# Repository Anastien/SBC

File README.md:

# SBC
My design of a single board computer.

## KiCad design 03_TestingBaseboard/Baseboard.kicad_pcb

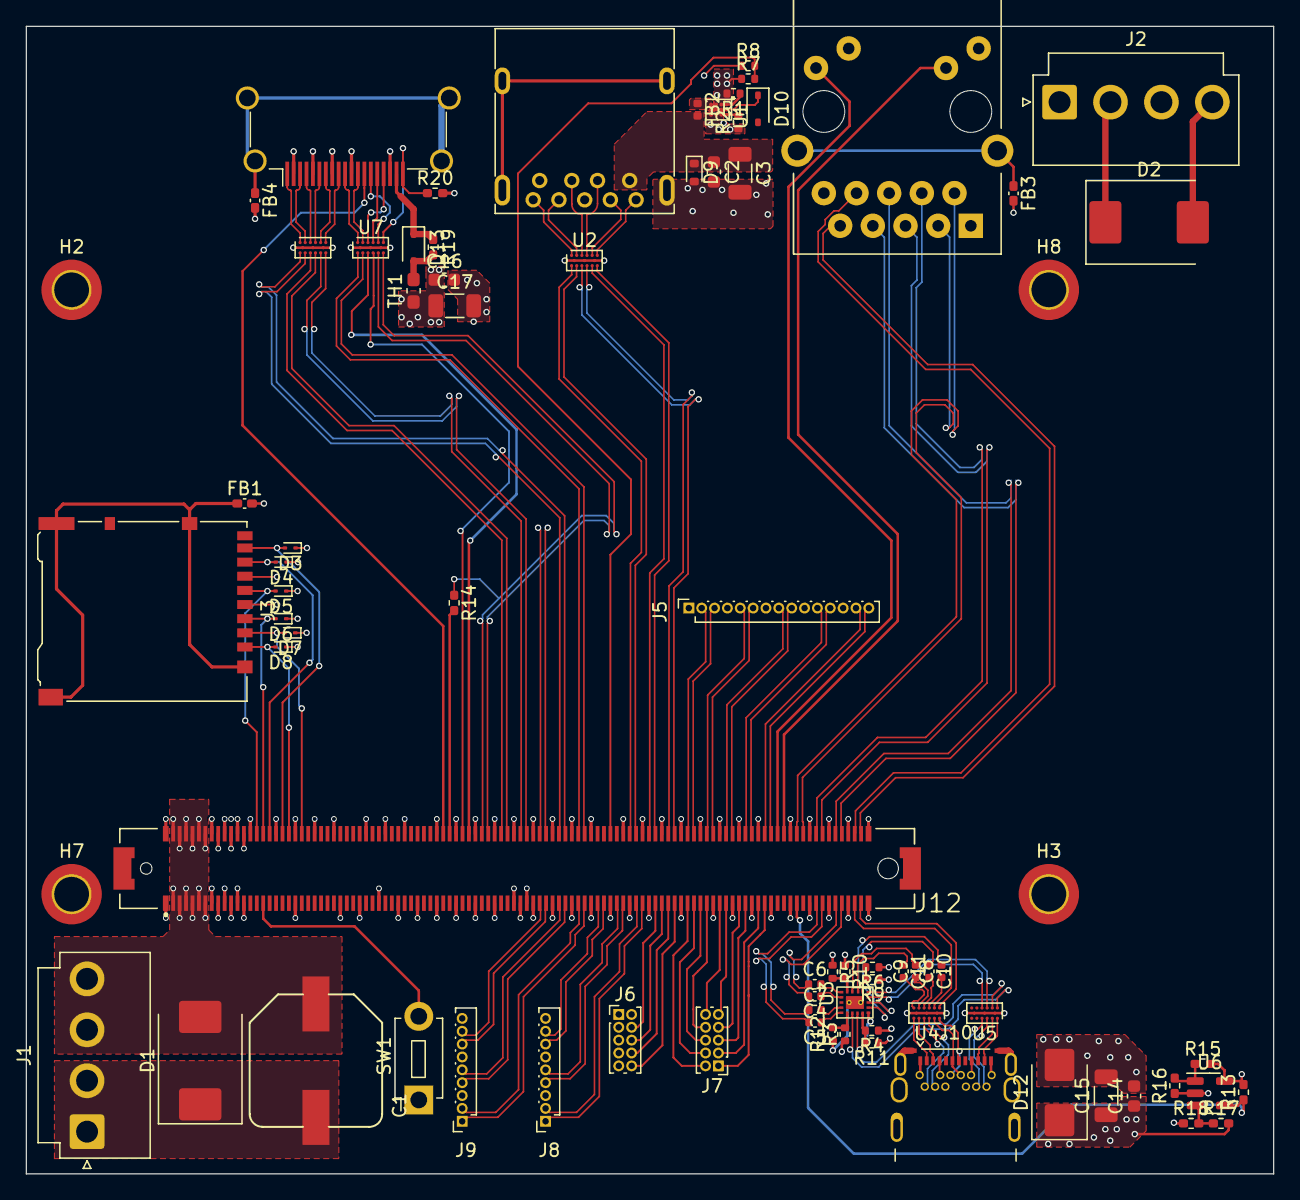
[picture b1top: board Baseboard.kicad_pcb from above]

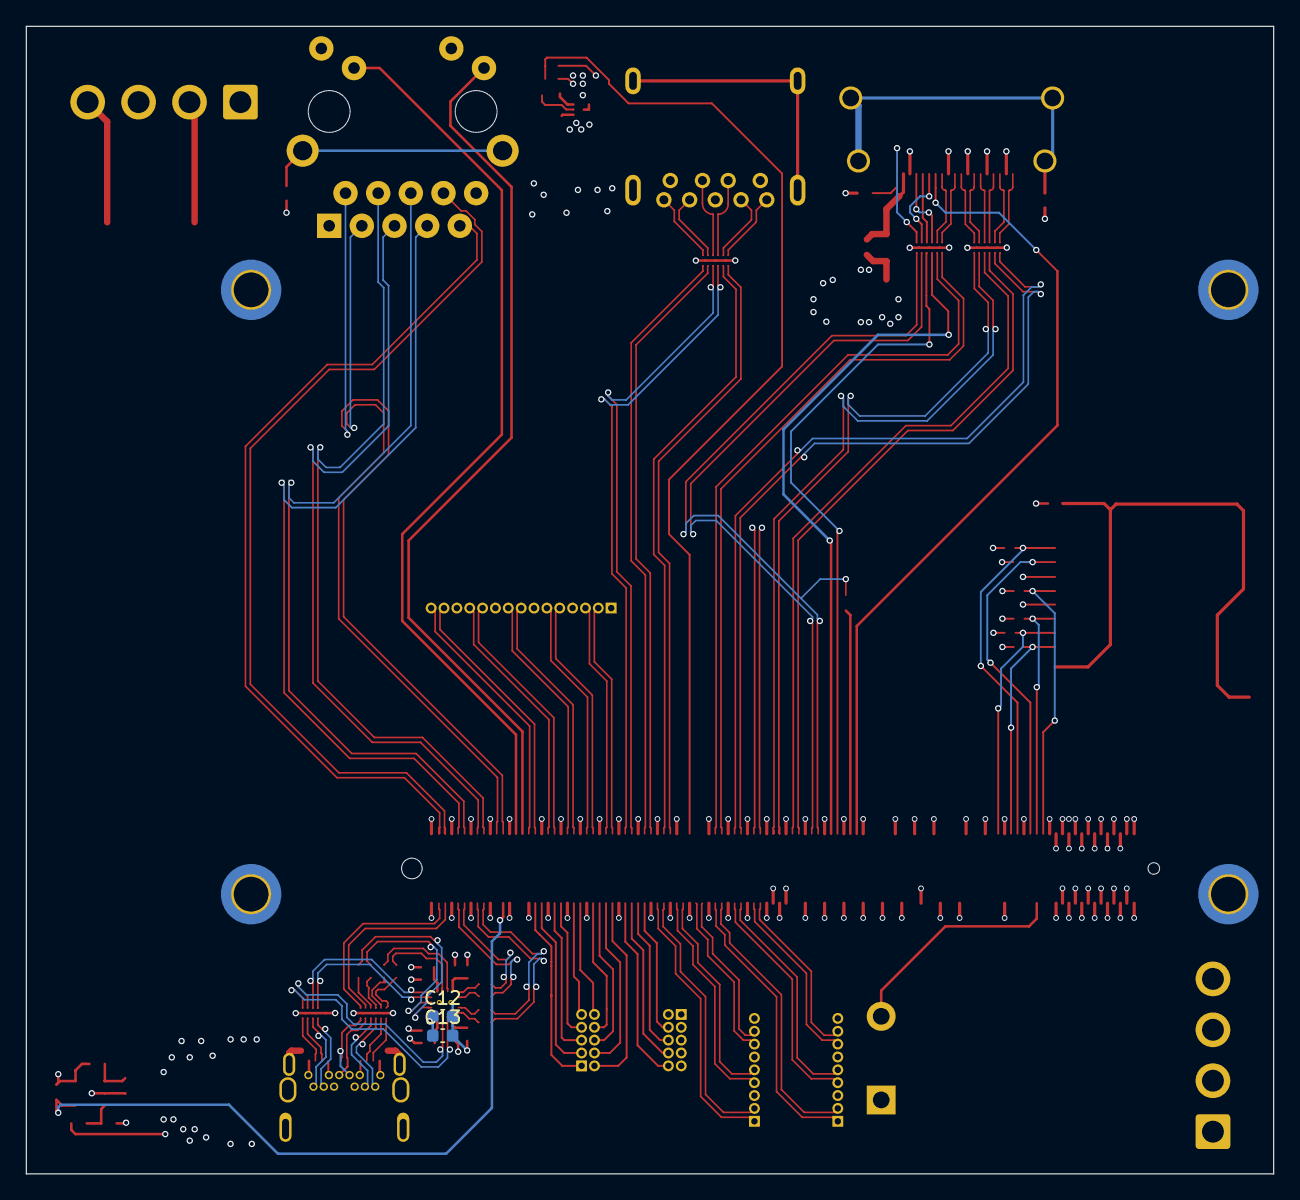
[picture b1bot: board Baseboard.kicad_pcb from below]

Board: 4 copper layers, 97.0 x 89.2 mm, 80 parts (2 on the bottom side), 146 nets.

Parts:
C1: 220uF; EEE-FK1H221GP
C2, C12, C13, C14, C16: 220nF; C_0603_1608Metric
C3, C15, C17: 10uF; C_1206_3216Metric
C4, C5, C6, C7, C8, C9, C10, C11: 220nF; C_0402_1005Metric
D1, D2: D_TVS; D_SMC
D3, D4, D5, D6, D7, D8: ESD9B3.3ST5G; D_SOD-923
D9: ESD5Zxx; D_SOD-523
D10, D13: SD0603S040S0R2; D_SOD-323
D12: SM6T24A; D_SMB
FB1, FB3, FB4: FerriteBead; L_0402_1005Metric_Pad0.77x0.64mm_HandSolder
FB2: FerriteBead_Small; L_0402_1005Metric
H2, H3, H7, H8: MountingHole_Pad; MountingHole_2.7mm_M2.5_DIN965_Pad_TopBottom
J1, J2: B4P-VH(LF)(SN); JST_VH_B4P-VH-B_1x04_P3.96mm_Vertical
J3: Micro_SD_Card_Det; microSD_HC_Hirose_DM3AT-SF-PEJM5
J4: USB3_A; USB3_A_Molex_48393-001
J5: Conn_01x15_Pin; PinSocket_1x15_P1.00mm_Vertical
J6, J7: Conn_02x05_Odd_Even; PinHeader_2x05_P1.00mm_Vertical
J8, J9: Conn_01x09_Pin; PinSocket_1x09_P1.00mm_Vertical
J10: USB_C_Receptacle; USB_C_Receptacle_CNCTech_C-ARA1-AK51X
J11: RJ45_RB1-125B8G1A; RJ45_UDE_RB1-125B8G1A
J12: 3-1827253-6; CONN_3-1827253-6
J13: HDMI_A; HDMI_A_Amphenol_10029449-x01xLF_Horizontal
R1: 10K; R_0402_1005Metric
R2, R7, R8: 24.3K; R_0402_1005Metric
R3, R4, R5, R6, R9, R10, R11, R12: 49.9; R_0402_1005Metric
R13, R14, R15, R16, R17, R18, R19: 49.9; R_0402_1005Metric_Pad0.72x0.64mm_HandSolder
R20: 1M; R_0402_1005Metric_Pad0.72x0.64mm_HandSolder
SW1: SW_Push; SW_PUSH_1P1T_6x3.5mm_H4.3_APEM_MJTP1243
TH1: Thermistor_PTC_US; Fuse_0603_1608Metric_Pad1.05x0.95mm_HandSolder
U1: NX5P3090; WLCSP12_1.65X1.35
U2, U4, U5, U7, U8: PCMF3USB3S; Nexperia_WLCSP-15_6-3-6_2.37x1.17mm_Layout6x3_P0.4mm
U3: PTN36043ABX; DHX2QFN18
U6: LM397; SOT-23-5

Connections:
+1V8: C12.1, C13.1, R3.1, R4.1, R5.1, R6.1, U3.5 (VDD1V8)
+5V: C16.1, C17.1, D2.2 (A2), J2.3, J2.4, R1.2, R7.1, R13.2, R15.2, TH1.1, U1.B1 (VIN1), U1.B2 (VIN2), U1.C1 (VIN3), U6.5 (V+)
/BASEBOARD/AP_N: C6.2, U3.14 (TX_AP-)
/BASEBOARD/AP_P: C4.1, U3.15 (TX_AP+)
/BASEBOARD/C_VBUS: C14.1, C15.1, D12.1 (A1), J10.A4 (VBUS), J10.A9 (VBUS), J10.B4 (VBUS), J10.B9 (VBUS), R17.2
/BASEBOARD/D1_N: J4.2 (D-), U2.A4 (CH2_IN-)
/BASEBOARD/D1_P: J4.3 (D+), U2.A3 (CH2_IN+)
/BASEBOARD/HC_N: J13.12 (CK-), U7.A2 (CH1_IN-)
/BASEBOARD/HC_P: J13.10 (CK+), U7.A1 (CH1_IN+)
/BASEBOARD/HDMI_5V: D13.1 (K), J13.18 (+5V), R19.1
/BASEBOARD/HEAC_N: J13.19 (HPD), R20.1, U7.A6 (CH3_IN-)
/BASEBOARD/HEAC_P: J13.14 (UTILITY), U7.A5 (CH3_IN+)
/BASEBOARD/HSCL: J13.15 (SCL), U7.A4 (CH2_IN-)
/BASEBOARD/HSDA: J13.16 (SDA), U7.A3 (CH2_IN+)
/BASEBOARD/HTX0_N: J13.9 (D0-), U8.A6 (CH3_IN-)
/BASEBOARD/HTX0_P: J13.7 (D0+), U8.A5 (CH3_IN+)
/BASEBOARD/HTX1_N: J13.6 (D1-), U8.A4 (CH2_IN-)
/BASEBOARD/HTX1_P: J13.4 (D1+), U8.A3 (CH2_IN+)
/BASEBOARD/HTX2_N: J13.3 (D2-), U8.A2 (CH1_IN-)
/BASEBOARD/HTX2_P: J13.1 (D2+), U8.A1 (CH1_IN+)
/BASEBOARD/LED0: J11.L3, J12.B97 (SPI_CS#_(**))
/BASEBOARD/LED1: J11.L1, J12.B96 (RSVD)
/BASEBOARD/RX1_N: J4.5 (SSRX-), U2.A1 (CH1_IN+)
/BASEBOARD/RX1_P: J4.6 (SSRX+), U2.A2 (CH1_IN-)
/BASEBOARD/RXC_N: U3.3 (RX_CON_1-), U5.C2 (CH1_OUT-)
/BASEBOARD/RXC_P: U3.2 (RX_CON_1+), U5.C1 (CH1_OUT+)
/BASEBOARD/RX_C2_N: U3.8 (RX_CON_2-), U5.C4 (CH2_OUT-)
/BASEBOARD/RX_C2_P: U3.9 (RX_CON_2+), U5.C3 (CH2_OUT+)
/BASEBOARD/R_AP_N: C7.2, U3.17 (RX_AP-)
/BASEBOARD/R_AP_P: C5.1, U3.18 (RX_AP+)
/BASEBOARD/TX1_N: J4.8 (SSTX-), U2.A5 (CH3_IN+)
/BASEBOARD/TX1_P: J4.9 (SSTX+), U2.A6 (CH3_IN-)
/BASEBOARD/TXC1_N: C10.1, U3.7 (TX_CON_1-)
/BASEBOARD/TXC1_P: C8.2, U3.6 (TX_CON_1+)
/BASEBOARD/TXC2_N: C11.1, U3.11 (TX_CON_2-)
/BASEBOARD/TXC2_P: C9.2, U3.12 (TX_CON_2+)
/BASEBOARD/U1RX1_N: J10.B11 (RX1+), U4.A4 (CH2_IN-)
/BASEBOARD/U1RX1_P: J10.B10 (RX1-), U4.A3 (CH2_IN+)
/BASEBOARD/U1_VBUS: C2.1, C3.1, D9.1 (K), FB2.2, J4.1 (VBUS)
/BASEBOARD/U2D_N: J10.A6 (D+), J10.B6 (D+), U4.A2 (CH1_IN-)
/BASEBOARD/U2D_P: J10.A7 (D-), J10.B7 (D-), U4.A1 (CH1_IN+)
/BASEBOARD/U2RX2_N: J10.A10 (RX2-), U5.A2 (CH1_IN-)
/BASEBOARD/U2RX2_P: J10.A11 (RX2+), U5.A1 (CH1_IN+)
/BASEBOARD/U2TX1_N: J10.A3 (TX1-), U4.A5 (CH3_IN+)
/BASEBOARD/U2TX1_P: J10.A2 (TX1+), U4.A6 (CH3_IN-)
/BASEBOARD/U2TX2_N: J10.B3 (TX2-), U5.A4 (CH2_IN-)
/BASEBOARD/U2TX2_P: J10.B2 (TX2+), U5.A3 (CH2_IN+)
/BASEBOARD/_TXC1_N: C10.2, U4.C4 (CH2_OUT-)
/BASEBOARD/_TXC1_P: C8.1, U4.C3 (CH2_OUT+)
/BASEBOARD/_TXC2_N: C11.2, U4.C6 (CH3_OUT-)
DSI_CLK_N: J5.3, J12.B83 (eDP/LVDS_BKLT_CTRL)
DSI_CLK_P: J5.2, J12.B82 (DDI0_PAIR3-)
DSI_D0_N: J5.12, J12.B92 (DDI0_PAIR5-_(*))
DSI_D0_P: J5.11, J12.B91 (DDI0_PAIR5+_(*))
DSI_D1_N: J5.9, J12.B89 (DD0_HPD)
DSI_D1_P: J5.8, J12.B88 (BIOS_DIS1#)
DSI_D2_N: J5.15, J12.B95 (DDI0_DDC_AUX_SEL)
DSI_D2_P: J5.14, J12.B94 (DDI0_PAIR6-_(*))
DSI_D3_N: J5.6, J12.B86 (VCC_5V_SBY)
DSI_D3_P: J5.5, J12.B85 (VCC_5V_SBY)
GBE0_MDI0_N: J11.R3 (TD1-), J12.B100 (GND(FIXED))
GBE0_MDI0_P: J11.R2 (TD1+), J12.B99 (DDI0_CTRLDATA_AUX-)
GBE0_MDI1_N: J11.R5 (TD2-), J12.B103 (SLEEP#)
GBE0_MDI1_P: J11.R4 (TD2+), J12.B102 (FAN_TACHIN)
GBE0_MDI2_N: J11.R7 (TD3-), J12.B106 (VCC_12V)
GBE0_MDI2_P: J11.R6 (TD3+), J12.B105 (VCC_12V)
GBE0_MDI3_N: J11.R9 (TD4-), J12.B109 (VCC_12V)
GBE0_MDI3_P: J11.R8 (TD4+), J12.B108 (VCC_12V)
GND: C1.2, C2.2, C3.2, C12.2, C13.2, C14.2, C15.2, C16.2, C17.2, D1.1 (A1), D2.1 (A1), D3.1 (A1), D4.1 (A1), D5.1 (A1), D6.1 (A1), D7.1 (A1), D8.1 (A1), D9.2 (A), D12.2 (A2), FB1.2, FB3.2, FB4.2, J1.1, J1.2, J2.1, J2.2, J3.6 (VSS), J4.4 (GND), J4.7 (DRAIN), J4.10 (SHIELD), J5.1, J5.4, J5.7, J5.10, J5.13, J6.1, J6.3, J6.5, J6.7, J6.9, J8.3, J8.6, J8.9, J9.3, J9.6, J9.9, J10.A1 (GND), J10.A12 (GND), J10.B1 (GND), J10.B12 (GND), J10.S1 (SHIELD), J12.A1 (GND(FIXED)), J12.A8 (GBE0_LINK#), J12.A9 (GBE0_MDI1-), J12.A10 (GBE0_MDI1+), J12.A11 (GND(FIXED)), J12.A12 (GBE0_MDI0-), J12.A13 (GBE0_MDI0+), J12.A21 (GND(FIXED)), J12.A28 ((S)ATA_ACT#), J12.A31 (GND(FIXED)), J12.A34 (BIOS_DIS0#), J12.A37 (USB6+), J12.A40 (USB1_RX_P), J12.A43 (USB1_TX_P), J12.A46 (USB1_DP), J12.A49 (EXCD0_CPPE#), J12.A52 (RSVD), J12.A55 (RSVD), J12.A56 (RSVD), J12.A57 (GND), J12.A58 (PCIE_TX3+), J12.A61 (PCIE_TX2+), J12.A64 (PCIE_TX1+), J12.A67 (GPI2), J12.A70 (GND(FIXED)), J12.A73 (eDP_TX1+/LVDS_A1+), J12.A76 (eDP_TX0-/LVDS_A2-), J12.A81 (eDP_TX3+/LVDS_A_CK+), J12.A86 (RSVD), J12.A89 (PCIE_CLK_REF-), J12.A92 (SPI_MISO_(**)), J12.A95 (SPI_MOSI_(**)), J12.A98 (SER0_TX_(**)), J12.A101 (SER1_TX_(**)), J12.A104 (VCC_12V), J12.A107 (VCC_12V), J12.A110 (GND(FIXED)), J12.B1 (GND(FIXED)), J12.B8 (LPC_DRQ0#_(*)), J12.B9 (LPC_DRQ1#_(*)), J12.B10 (LPC_CLK), J12.B11 (GND(FIXED)), J12.B12 (PWRBTN#), J12.B13 (SMB_CK), J12.B14 (SMB_DAT), J12.B18 (SUS_STAT#), J12.B21 (GND(FIXED)), J12.B24 (PWR_OK), J12.B27 (WDT), J12.B32 (SPKR), J12.B35 (THRM#), J12.B38 (USB_4_5_OC#), J12.B43 (USB3+), J12.B46 (USB1+), J12.B49 (SYS_RESET#), J12.B52 (RSVD), J12.B55 (RSVD), J12.B58 (PCIE_RX3+), J12.B61 (PCIE_RX2+), J12.B64 (PCIE_RX1+), J12.B67 (WAKE1#_(**)), J12.B72 (DDI0_PAIR0-), J12.B75 (DDI0_PAIR2+), J12.B78 (DDI0_PAIR4-_(*)), J12.B81 (DDI0_PAIR3+), J12.B84 (VCC_5V_SBY), J12.B87 (VCC_5V_SBY), J12.B90 (GND(FIXED)), J12.B93 (DDI0_PAIR6+_(*)), J12.B98 (DDI0_CTRLCLK_AUX+), J12.B101 (FAN_PWMOUT), J12.B104 (VCC_12V), J12.B107 (VCC_12V), J12.B110 (GND(FIXED)), J13.2 (D2S), J13.5 (D1S), J13.8 (D0S), J13.11 (CKS), J13.17 (GND), R2.1, R8.1, R9.1, R10.1, R11.1, R12.1, R16.1, R18.1, R20.2, SW1.1, U1.B3 (GND1), U1.C3 (GND2), U1.D3 (GND3), U2.B1 (GND_CH1), U2.B2 (GND_CH2), U2.B3 (GND_CH3), U3.19 (GND), U4.B1 (GND_CH1), U4.B2 (GND_CH2), U4.B3 (GND_CH3), U5.B1 (GND_CH1), U5.B2 (GND_CH2), U5.B3 (GND_CH3), U6.2 (V-), U7.B1 (GND_CH1), U7.B2 (GND_CH2), U7.B3 (GND_CH3), U8.B1 (GND_CH1), U8.B2 (GND_CH2), U8.B3 (GND_CH3)
HDMI_AUX_N: J12.B50 (CB_RESET#), R14.1, U7.C6 (CH3_OUT-)
HDMI_AUX_P: J12.B51 (GND(FIXED)), U7.C5 (CH3_OUT+)
HDMI_CEC: J12.B44 (USB_0_1_OC#), J13.13 (CEC)
HDMI_HDP: J12.B45 (USB1-), R14.2
HDMI_SCL: J12.B47 (EXCD1_PERST#), U7.C4 (CH2_OUT-)
HDMI_SDA: J12.B48 (EXCD1_CPPE#), U7.C3 (CH2_OUT+)
HDMI_TX0_N: J12.B56 (RSVD), U8.C6 (CH3_OUT-)
HDMI_TX0_P: J12.B57 (GPO2), U8.C5 (CH3_OUT+)
HDMI_TX1_N: J12.B54 (GPO1), U8.C4 (CH2_OUT-)
HDMI_TX1_P: J12.B53 (RSVD), U8.C3 (CH2_OUT+)
HDMI_TX2_N: J12.B62 (PCIE_RX2-), U8.C2 (CH1_OUT-)
HDMI_TX2_P: J12.B63 (GPO3), U8.C1 (CH1_OUT+)
HDMI_TX3_N: J12.B66 (WAKE0#), U7.C2 (CH1_OUT-)
HDMI_TX3_P: J12.B65 (PCIE_RX1-), U7.C1 (CH1_OUT+)
HOST_PCIE1_CLK_N: J9.1, J12.A66 (GND)
HOST_PCIE1_CLK_P: J9.2, J12.A65 (PCIE_TX1-)
HOST_PCIE2_CLK_N: J8.7, J12.A69 (PCIE_TX0-)
HOST_PCIE2_CLK_P: J8.8, J12.A68 (PCIE_TX0+)
unnamed: D10.1 (K), U1.A2 (#FLT)
unnamed: D13.2 (A), R19.2, TH1.2
unnamed: FB3.1, J11.SH
unnamed: FB4.1, J13.SH
unnamed: FB1.1, J3.11 (SHIELD)
unnamed: R1.1, U1.A1 (EN)
unnamed: R2.2, U1.A3 (IL)
unnamed: FB2.1, U1.C2 (VBUS1), U1.D1 (VBUS2), U1.D2 (VBUS3)
unnamed: R3.2, R12.2, U3.1 (RXDE)
unnamed: R6.2, R9.2, U3.10 (RXEQ)
unnamed: R5.2, R10.2, U3.13 (TXDE)
unnamed: R4.2, R11.2, U3.4 (TXEQ)
unnamed: C9.1, U4.C5 (CH3_OUT+)
unnamed: R17.1, R18.2, U6.3 (+)
unnamed: R15.1, R16.2, U6.1 (-)
PCIE1_RXN: J9.8, J12.A59 (PCIE_TX3-)
PCIE1_RXP: J9.7, J12.A60 (GND(FIXED))
PCIE1_TXN: J9.5, J12.A62 (PCIE_TX2-)
PCIE1_TXP: J9.4, J12.A63 (GPI1)
PCIE2_RXN: J8.4, J12.A72 (eDP_TX2-/LVDS_A0-)
PCIE2_RXP: J8.5, J12.A71 (eDP_TX2+/LVDS_A0+)
PCIE2_TXN: J8.1, J12.A75 (eDP_TX0+/LVDS_A2+)
PCIE2_TXP: J8.2, J12.A74 (eDP_TX1-/LVDS_A1-)
SD2_CLK: D5.2 (A2), J3.5 (CLK), J12.B15 (SMB_ALERT#)
SD2_CMD: D6.2 (A2), J3.3 (CMD), J12.B16 (SATA1_TX+)
SD2_D0: D4.2 (A2), J3.7 (DAT0), J12.B17 (SATA1_TX-)
SD2_D1: D3.2 (A2), J3.8 (DAT1), J12.B19 (SATA1_RX+)
SD2_D2: D8.2 (A2), J3.1 (DAT2), J12.B20 (SATA1_RX-)
SD2_D3: D7.2 (A2), J3.2 (DAT3/CD), J12.B22 (USB_SSTX0-)
SPI1_MISO: J6.4, J12.A77 (eDP/LVDS_VDD_EN)
SPI1_MOSI: J6.6, J12.A78 (LVDS_A3+)
SPI1_SCLK: J6.10, J12.A80 (GND(FIXED))
SPI1_SSO: J6.8, J12.A79 (LVDS_A3-)
SPI2_MISO: J7.2, J12.A82 (eDP_TX3-/LVDS_A_CK-)
SPI2_MOSI: J7.4, J12.A83 (eDP_AUX+/LVDS_I2C_CK)
SPI2_SCLK: J7.8, J12.A85 (GPI3)
SPI2_SSO: J7.6, J12.A84 (eDP_AUX-/LVDS_I2C_DAT)
SYS_NRST: J12.A16 (SATA0_TX+), SW1.2
UART1_RXD: J7.3, J12.A93 (GPO0)
UART1_TXD: J7.1, J12.A94 (SPI_CLK_(**))
UART2_RXD: J7.9, J12.A88 (PCIE_CLK_REF+)
UART2_TXD: J7.10, J12.A87 (eDP_HPD)
UART3_RXD: J7.7, J12.A90 (GND(FIXED))
UART3_TXD: J7.5, J12.A91 (SPI_POWER)
USB1_DN: J12.B79 (eDP/LVDS_BKLT_EN), U2.C4 (CH2_OUT-)
USB1_DP: J12.B80 (GND(FIXED)), U2.C3 (CH2_OUT+)
USB1_RX_N: J12.B73 (DDI0_PAIR1+), U2.C1 (CH1_OUT+)
USB1_RX_P: J12.B74 (DDI0_PAIR1-), U2.C2 (CH1_OUT-)
USB1_TX_N: J12.B76 (DDI0_PAIR2-), U2.C5 (CH3_OUT+)
USB1_TX_P: J12.B77 (DDI0_PAIR4+_(*)), U2.C6 (CH3_OUT-)
USB1_VBUS: J12.B70 (GND(FIXED)), R7.2, R8.2
USB2_DN: J12.A108 (VCC_12V), U4.C2 (CH1_OUT-)
USB2_DP: J12.A109 (VCC_12V), U4.C1 (CH1_OUT+)
USB2_RX_N: C7.1, J12.A102 (SER1_RX_(**))
USB2_RX_P: C5.2, J12.A103 (LID#)
USB2_TX_N: C6.1, J12.A105 (VCC_12V)
USB2_TX_P: C4.2, J12.A106 (VCC_12V)
USB2_VBUS: J12.A99 (SER0_RX_(**)), R13.1, U6.4
VIN: C1.1, D1.2 (A2), J1.3, J1.4, J12.A2 (GBE0_MDI3-), J12.A3 (GBE0_MDI3+), J12.A4 (GBE0_LINK100#), J12.A5 (GBE0_LINK1000#), J12.A6 (GBE0_MDI2-), J12.A7 (GBE0_MDI2+), J12.B2 (GBE0_ACT#), J12.B3 (SPI0_NCS0), J12.B4 (SPI0_IO0), J12.B5 (SPI0_IO1), J12.B6 (SPI0_IO2), J12.B7 (SPI0_IO3)

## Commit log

2023-09-03 Init.
2023-09-03 Update.
2023-09-07 UPDATE TO POWER TREE.
2023-09-07 UPDATE, FULL ROUTING!
2023-09-10 Update!
2023-09-10 ADDING WIFI+BLUETOOTH.
2023-12-23 Skew Check.
2024-01-23 Regular Update.
